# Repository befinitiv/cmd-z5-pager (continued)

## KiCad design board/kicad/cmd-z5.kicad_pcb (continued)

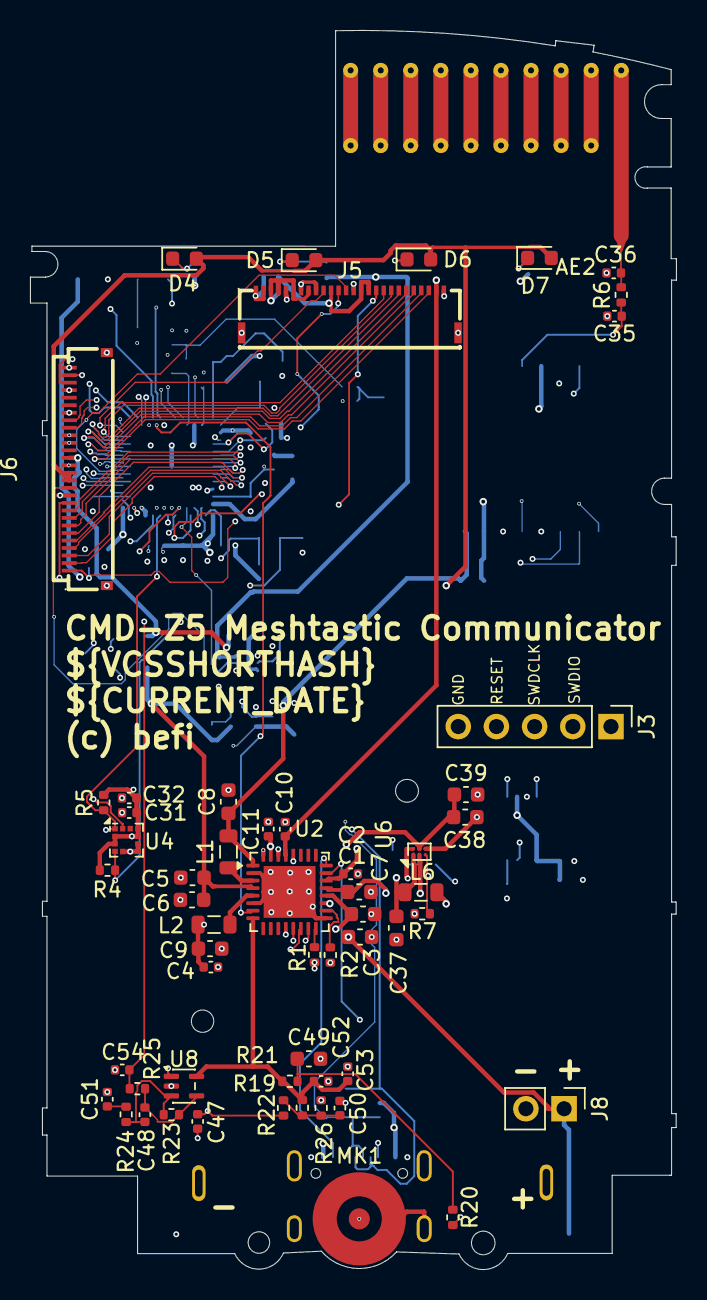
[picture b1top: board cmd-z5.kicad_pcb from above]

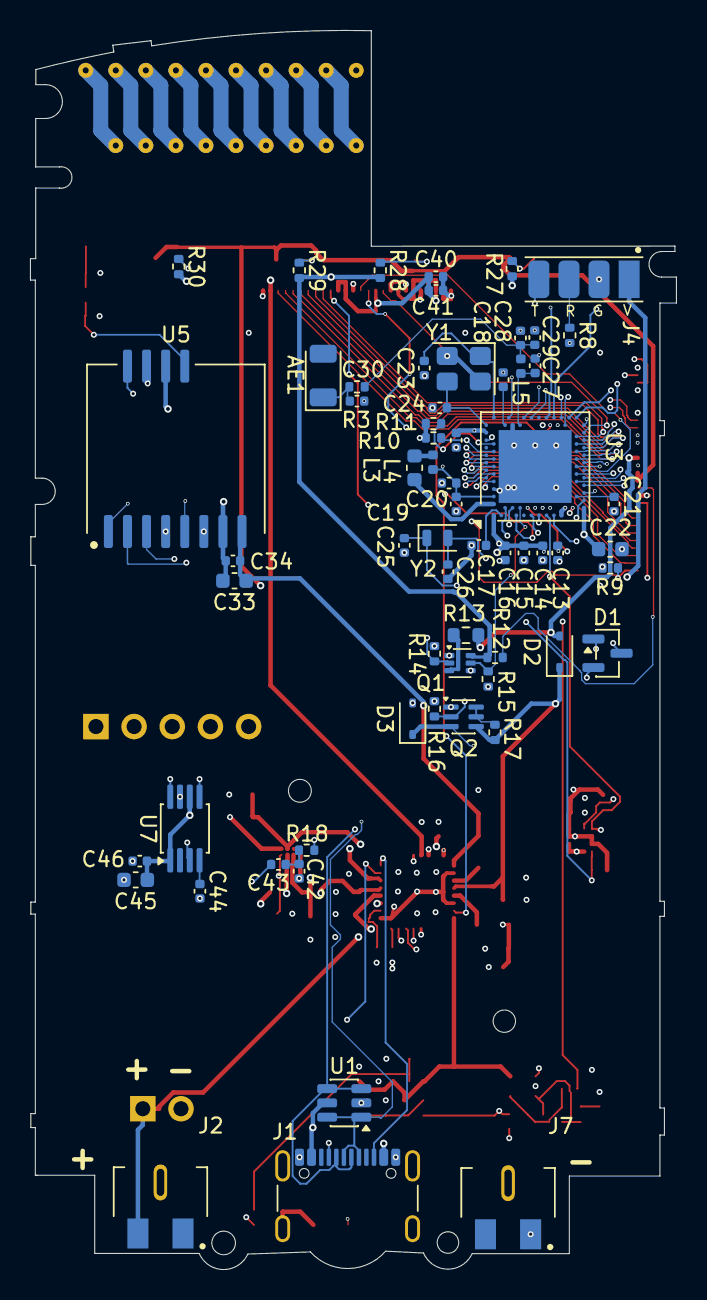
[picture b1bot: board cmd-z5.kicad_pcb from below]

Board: 6 copper layers, 43.0 x 82.4 mm, 120 parts (63 on the bottom side), 107 nets.

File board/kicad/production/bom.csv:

Designator,Footprint,Quantity,Value,LCSC Part #
AE1,Johanson_2450AT18x100,1,2450AT18A100E,C89334
AE2,Texas_SWRA416_868MHz_915MHz_Mirrored,1,PCB antenna 868/915 MHz,
C1,0603,1,1u,
"C10, C11, C13, C19, C2, C32, C40, C47, C50, C52",0402,10,1u,
"C12, C21, C51",0402,3,4.7u,
"C14, C15, C16, C17, C31, C34, C4, C41, C43, C44, C46, C53",0402,12,100n,
C18,0402,1,100p,
C20,0402,1,47n,
C22,0603,1,4.7u,
"C23, C24",0402,2,15p,
"C25, C26",0402,2,8.2p,
C27,0402,1,0.8p,
C28,0402,1,0.5p,
C3,0603,1,2.2u,
"C33, C37, C38, C39, C45, C49, C5, C6, C7, C8, C9, L3",0603,12,10u,
"C42, C54",0402,2,10n,
C48,0402,1,330p,
D1,SOT-23,1,BAT54C,C916424
"D2, D3",D_SOD-323,2,1N5819WS,C191023
"D4, D5, D6, D7",0603,4,green,C72043
J1,USB_C_Receptacle_GCT_USB4105-xx-A_16P_TopMnt_Horizontal,1,USB4105-GF-A,C3020560
"J2, J7",BAT-SMD_2P-P3.00_G-Switch_GT-BTP30002-0500B-015A,2,GT-BTP30002-0500B-015A,C41378718
J4,SolderPads_1x04_P2.00mm_SMD,1,TBS M10N,
J5,FPC-SMD_26P-P0.50_KH-FPC0.5-H1.0SMT-26P-QCHF,1,KH-FPC0.5-H1.0SMT-26P-QCHF,C3250122
J6,FPC-SMD_28P-P0.50_KH-FPC0.5-H1.0SMT-28P-QCHF,1,KH-FPC0.5-H1.0SMT-28P-QCHF,C3250123
"L1, L2, L6",0805,3,2.2u,
L4,0402,1,15n,
L5,0402,1,4.7n,
Q1,SOT-563,1,DMG1024UV,C2759893
Q2,SOT-363_SC-70-6,1,DMG1016UDW,C211433
R1,0402,1,150k 1%,
"R10, R11, R9",0402,3,10M,
"R12, R2, R3, R6",0402,4,0,
R13,0603,1,10,
"R14, R15, R16, R17, R21, R22, R23, R26",0402,8,100k,
"R18, R19, R25, R8",0402,4,1k,
"R20, R24",0402,2,2.2k,
"R27, R28, R29, R30",0402,4,330,
"R4, R5",0402,2,4.7k,
R7,0402,1,1M,
U1,SOT-23-6,1,USBLC6-2SC6,C7519
U2,QFN-32-1EP_5x5mm_P0.5mm_EP3.45x3.45mm,1,nPM1300-QEAA-R7,C7501206
U3,Nordic_AQFN-73-1EP_7x7mm_P0.5mm,1,nRF52840-QIAA-R,C190794
U4,LGA-12_2x2mm_P0.5mm,1,LIS2DH12TR,C110926
U5,Seeed_Wio-SX1262,1,Wio-SX1262,
U6,Texas_DSBGA-6_0.855x1.255mm_Layout2x3_P0.4mm_LevelB,1,TPS610997YFFR,C2072359
U7,MSOP-8_3x3mm_P0.65mm,1,PAM8302AASCR,C113367
U8,SOT-353_SC-70-5,1,TLV9001IDCKR,C398362
Y1,Crystal_SMD_3225-4Pin_3.2x2.5mm,1,32 MHz CL=10pF,C91742
Y2,Crystal_SMD_2012-2Pin_2.0x1.2mm,1,32.768 kHz CL=7pF,C99009
